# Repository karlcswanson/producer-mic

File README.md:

# producer-mic

This mic was created to meet a unique need for a push-to-talk mic for Shure wireless systems. In a live environment with high standards and attention to detail, they did not want the Executive Producer stand out with a comm headset and pack. They opted to go with a more covert IFB based solution.

For many years, a custom Countryman B3 filled this need. It was wired into two way radio surveillance kit. While simple, this design was fragile, difficult to repair, and caused pops when the mic was turned on and off. So I decided to make a microphone that was difficult to repair but at least did not pop when it turned on and off.

This tiny mic attaches to a sleeve using a magnet. Users are intelligible in loud production environments. The project was an overall success!

Below you will find a project design and build log. This repo contains design assets, schematics, board, and footprint libraries.

## Circuit Design

Shure sells inline mute switches, these are often used by NFL Refs to talk to America. A schematic is posted in their knowledge base. The additional caps and resistors in this circuit help clean up small voltage spikes when the switch changes state.

The B3 capsule in the previous iteration of the mic is expensive, especially when it is just used for comm! It was originally chosen for its size, but we can go much smaller!

### Microphone

Yes, that is a microphone on a lego stud! This is a Knowles SPH6611LR5H-1 MEMS microphone. This $0.92 component is constructed using processes similar to how microprocessors are made. The diaphragm and amplifier are etched out of silicon. This particular component is bottom ported, the audio passes through the bottom of the PCB into the microphone.

### Switch
For a Push-To-Talk, the switch needs to be normally closed. Pressing the button opens the switch to un-mute. A SPST NC or SPDT switch is required. The NKK G3B15AH-R-YA was selected, it is a SMT right angle switch. Its a bit larger than I'd like but there are not as many options for SPDT right angle SMT switches.

## Schematic

I start by recreating the schematic for the Shure mute switch in [KiCad](https://www.kicad.org). There is one additional resistor to add. The microphone runs at 1.5V - 3.6V. We need to reduce the 5V DC bias from the bodypack into to that range.

|           |           |             |            |         |               |
|-----------|-----------|-------------|------------|---------|---------------|
| Vin       | 5 V       |             | R1         | 10000 Ω |               |
| Vmin      | 1.5 V     |             | R2         | 8000 Ω  |               |
| Vmax      | 3.6 V     |             | R3         | 20000 Ω |               |
| Idd@1.8 V | 0.000145A |             |            |         |               |
|           |           |             |            |         |               |
|           |           | Voltage Div |            |         | Current Limit |
|           | RbodyPack | Vout        | Idiv       |         | Vout          |
| ATXD      | 0         | 2.222 V     | 0.00027778 |         | 2.1 V         |
| ULXD      | 1000 Ω    | 2.105 V     | 0.00026316 |         | 1.955 V       |
| QLXD      | 1000 Ω    | 2.105 V     | 0.00026316 |         | 1.955 V       |
| UHFR      | 500 Ω     | 2.162 V     | 0.00027027 |         | 2.0275 V      |

Shure sells a few different lines of wireless systems. Each system has a slightly different bias circuit. Lets check if we can find a combination of resistors that works with all models. In Excel, I prototype regulating the voltage using a voltage divider (R1, R2) and a current limiting resistor (R3).  A 20kΩ current limiting resistor ends up fitting in perfectly. Its already used in the mute circuit and drops the voltage within the range required by the microphone.

## Component Footprints
KiCad includes footprints for many devices, but not all. Using the Footprint Editor, we create new layouts for the microphone and switch.

The microphone datasheet includes mechanical specifications, a pinout, and solder stencil pattern. Using these measurements and some basic math, we add pads that correspond to contacts on the microphone. The footprint editor lets us add pads to different layers of the footprint.

For the microphone, we define the footprint by these layers:
* Copper - This is where we want copper on the PCB.
* Mask - This is where we want copper to be exposed.
* Paste - Where we want solder paste to be applied. This will be later be used to create a stencil.
* Silkscreen - This layer adds labels, polarity indicators, and other info to the PCB.
* Drill - Where holes will be drilled. These are often used to connect between layers of the PCB. For the microphone, its also used to create an acoustic port.

Additional custom footprints are created for the artwork on the front of the mic and the PTT button.

## Design

I was looking at different triangle based patterns to put on the front of the mic. Could not get them to fit right. A few weeks later I found the perfect art deco pattern while on an architectural tour. This was found at the Town of Lake Water Tower and Municipal Building in Milwaukee Wisconsin.

## PCB Layout

Each symbol in the PCB layout has a corresponding footprint. These footprints are added to the PCB. I know where I want the mic, switch and pads for the cable to go so those are placed first. From there, I place the rest of the components.

After everything is placed, the nets are turned into routes. I use the Route tool draw a path between pads of different components. Ground is done last, for that I use a pour to fill in the rest of the space with ground.

## Fabrication

The KiCad file goes off to [OshPark](https://oshpark.com) to be fabricated. OshPark makes a panel that includes the producer-mic pcb along with pcbs from dozens of other customers. They make it very easy and affordable to run small prototypes, this board cost $1.70!

The KiCad file also gets uploaded to [OshStencil](https://www.oshstencils.com/). They'll etch a stainless steel solder paste stencil using the paste layer we defined earlier.

|  |  |
|-----------------------------|---------------------------------|
|  |  |

Time to solder it up! The stencil is placed over the PCB, and the paste is applied by spreading the paste across. The components are applied to the board using a set of precision tweezers. Placement does not need to be perfect, as the flux evaporates, the surface tension of the solder will kind of pull the components into place. It is very cool to see! The boards go onto the hotplate. As the paste heats up, it goes from a grayish color to a metallic silver. When everything is silver, the board is done and can be removed to cool down.

## Case Design and Construction

The board outline was brought into Adobe Illustrator to work out the case geometry. I also created a model in AutoDesk Fusion360. My friend Dan, a skilled cabinetmaker, was able to cut a few prototypes out of scrap plastic material using a cnc router. Once we had the fit right, it was cut out of wood.

The hole for the switch and wire are manually drilled and a magnet is glued to the inside of the case. The cable is fished in and soldered to the board. The board is glued in place. The mic is finished!

The mic worked well during its initial testing, but there was a bit of wind noise. I tried out a lav sized deadcat. There was a bit of improvement, but it didn't make up for the weird texture. I ended up going with a small piece of open cell foam that was locally sourced from the lid of my Pelican case. That seemed to resolve the issue.

## BOM
| **Description**        | **Model**      | **Manufacturer** | **Quantity** | **Price Each** | **Total Price** |
|------------------------|----------------|------------------|--------------|----------------|-----------------|
| 0.12uF 805 capacitor   | 08053C124JAT2A | KYOCERA AVX      | 1            | $0.24          | $0.24           |
| 150pF 805 capacitor    | 08051A151J4T4A | KYOCERA AVX      | 1            | $0.16          | $0.16           |
| MEMS microphone        | SPH6611LR5H-1  | Knowles          | 1            | $0.92          | $0.92           |
| 20k 805 Resistor       | ERJ-6ENF2002V  | Panasonic        | 2            | $0.03          | $0.06           |
| 100k 805 Resistor      | ERJ-6ENF1003V  | Panasonic        | 1            | $0.03          | $0.03           |
| SPDT Switch            | G3B15AH-R-YA   | NKK              | 1            | $6.60          | $6.60           |
| PCB                    |                | OSHPark          | 1            | $1.70          | $1.70           |
| TA4F Connector         | RT4FC-B        | Neutrik          | 1            | $2.80          | $2.80           |
| Balanced Lav Mic Cable | W2901          | Mogami           | 6            | $0.67          | $4.02           |
|                        |                |                  |              |                |                 |
|                        |                |                  |              | **Total:**     | $16.53          |

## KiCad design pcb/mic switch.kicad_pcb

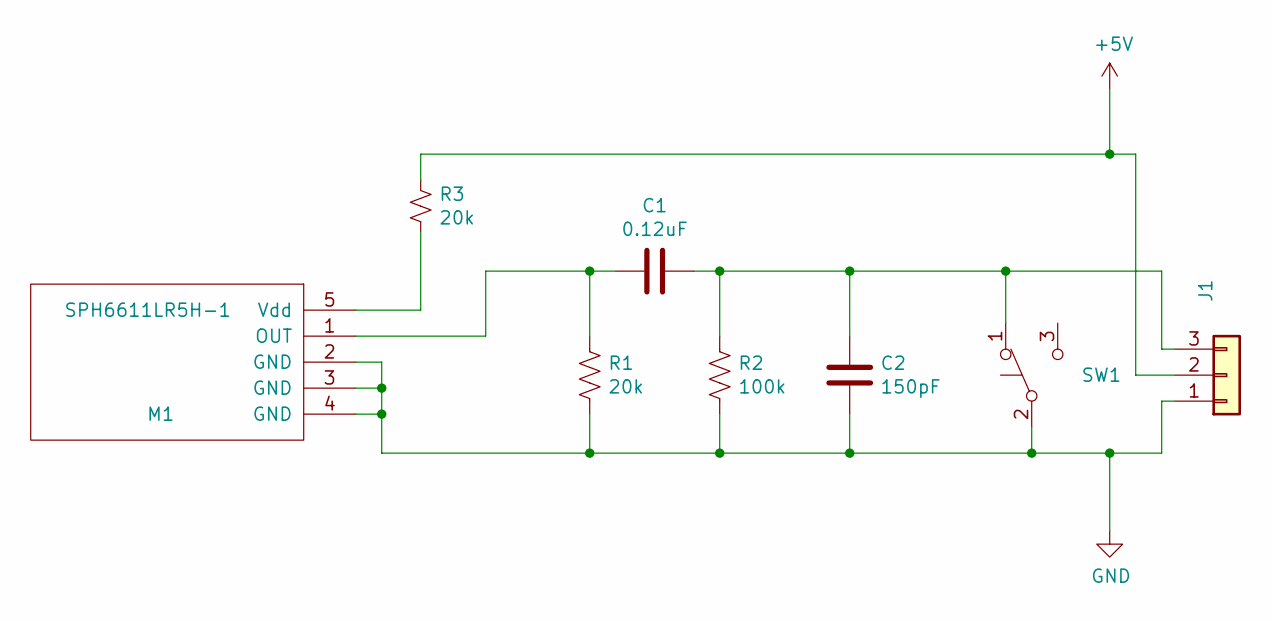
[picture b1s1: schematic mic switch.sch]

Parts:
C1: 0.12uF; C_0805
C2: 150pF; C_0805
J1: Conn_01x03; SMT-CON
M1: SPH6611LR5H-1
R1, R3: 20k; R_0805
R2: 100k; R_0805
SW1: SW_Push_SPDT; G3B15AH-R-YA

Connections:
+5V: J1.2, R3.1
GND: C2.2, J1.1, M1.2 (GND), M1.3 (GND), M1.4 (GND), R1.2, R2.2, SW1.2 (B), SW1.4
unnamed: C1.1, C2.1, J1.3, R2.1, SW1.1 (A)
unnamed: C1.2, M1.1 (OUT), R1.1
unnamed: M1.5 (Vdd), R3.2

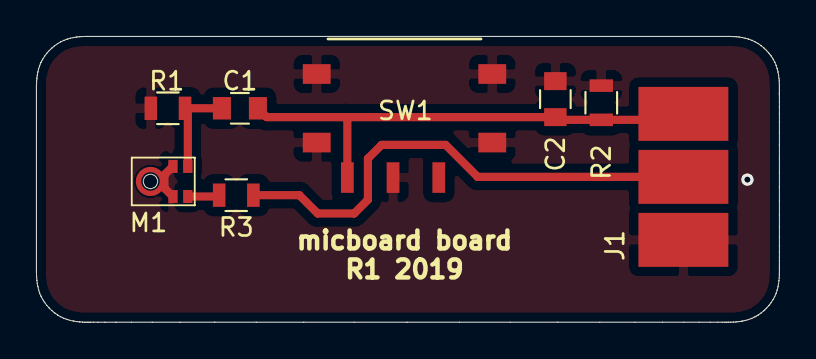
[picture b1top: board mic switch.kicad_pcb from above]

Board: 2 copper layers, 41.3 x 15.9 mm, 8 parts (0 on the bottom side), 5 nets.

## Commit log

2025-03-24 start on doc
2025-03-25 add datatable
2025-03-25 add pictures
2025-03-27 footprint
2025-03-27 copy edits
2025-03-27 add hero img
2025-03-28 adds
2025-03-28 copy updates
2025-03-28 outlines
2025-03-28 Add BOM
2025-03-28 fixbom
2025-03-29 readme update
2025-03-29 add pcb files
2025-03-29 gitignore
2025-03-29 edits
